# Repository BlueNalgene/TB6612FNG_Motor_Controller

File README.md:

# TB6612FNG_Motor_Controller
This repository includes the designs for an open source TB6612FNG motor controller breakout board.

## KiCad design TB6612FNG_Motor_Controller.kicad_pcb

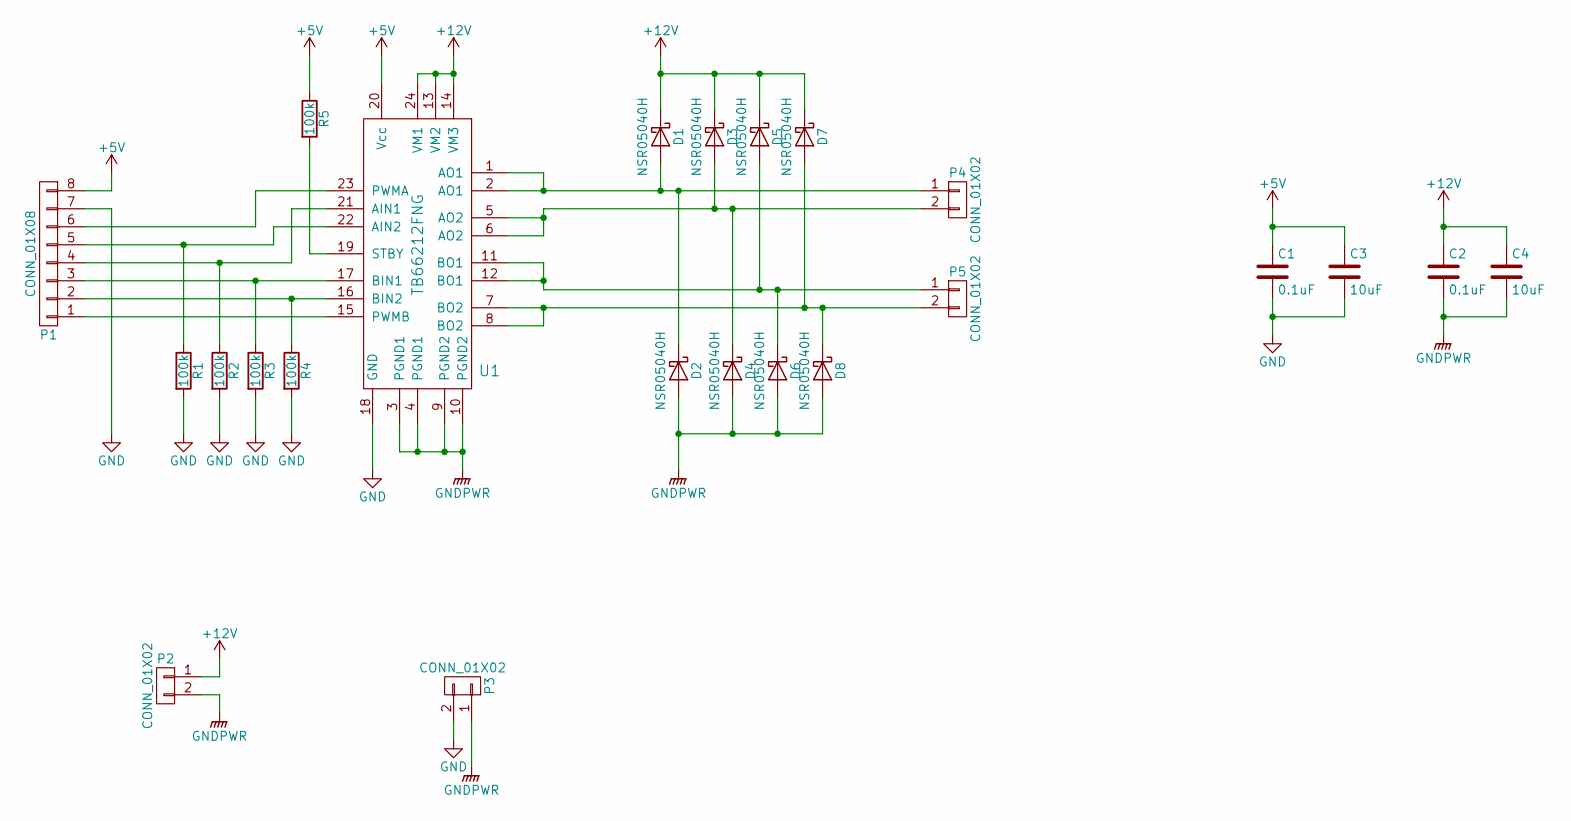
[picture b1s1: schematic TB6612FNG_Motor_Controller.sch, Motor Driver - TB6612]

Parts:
C1, C2: 0.1uF; C_0805_HandSoldering
C3, C4: 10uF; C_0805_HandSoldering
D1, D2, D3, D4, D5, D6, D7, D8: NSR05040H; D_SOD-323_HandSoldering
P1: CONN_01X08; Pin_Header_Straight_1x08
P2: CONN_01X02; TerminalBlock_Pheonix_MKDS1.5-2pol
P3: CONN_01X02; C_0603
P4, P5: CONN_01X02; Pin_Header_Straight_1x02
R1, R2, R3, R4, R5: 100k; R_0805_HandSoldering
U1: TB66212FNG; SSOP-24_5.3x8.2mm_Pitch0.65mm

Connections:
+5V: C1.1, C3.1, P1.8, R5.1, U1.20 (Vcc)
+12V: C2.1, C4.1, D1.1 (K), D3.1 (K), D5.1 (K), D7.1 (K), P2.1, U1.13 (VM2), U1.14 (VM3), U1.24 (VM1)
GND: C1.2, C3.2, P1.7, P3.2, R1.2, R2.2, R3.2, R4.2, U1.18 (GND)
GNDPWR: C2.2, C4.2, D2.2 (A), D4.2 (A), D6.2 (A), D8.2 (A), P2.2, P3.1, U1.3 (PGND1), U1.4 (PGND1), U1.9 (PGND2), U1.10 (PGND2)
unnamed: D1.2 (A), D2.1 (K), P4.1, U1.1 (AO1), U1.2 (AO1)
unnamed: D3.2 (A), D4.1 (K), P4.2, U1.5 (AO2), U1.6 (AO2)
unnamed: D5.2 (A), D6.1 (K), P5.1, U1.11 (BO1), U1.12 (BO1)
unnamed: D7.2 (A), D8.1 (K), P5.2, U1.7 (BO2), U1.8 (BO2)
unnamed: P1.1, U1.15 (PWMB)
unnamed: P1.2, R4.1, U1.16 (BIN2)
unnamed: P1.3, R3.1, U1.17 (BIN1)
unnamed: P1.4, R2.1, U1.21 (AIN1)
unnamed: P1.5, R1.1, U1.22 (AIN2)
unnamed: P1.6, U1.23 (PWMA)
unnamed: R5.2, U1.19 (STBY)

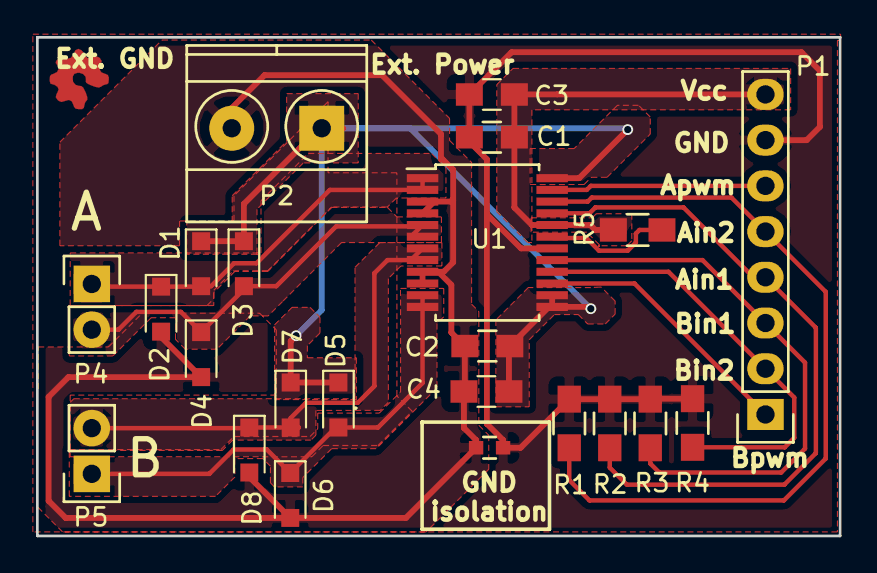
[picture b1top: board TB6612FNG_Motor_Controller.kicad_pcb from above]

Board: 2 copper layers, 44.6 x 27.7 mm, 23 parts (0 on the bottom side), 15 nets.

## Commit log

2018-02-14 Initial Upload
2018-02-14 Gerber files, initial commit
2018-03-04 added CAD files for laser cutting soldermask
